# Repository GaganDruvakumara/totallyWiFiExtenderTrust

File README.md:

# Totally A Wifi Extender

### Key Features
* It extends your WiFi
* It uses USB A
* It has a range of a 1-3 meters
* No batteries required
* It makes the range of your WiFi bigger

## PCB
Front (back is just silkscreen & USB pads, you can see in 3d model)

Front

Back

## Bill of Materials
| Reference | Qty | Part                              | Footprint                                                               | Unit Price (USD) | Total Price (USD) |
| --------- | --- | --------------------------------- | ----------------------------------------------------------------------- | ---------------- | ----------------- |
| AE1       | 1   | Antenna                           | RF_Antenna:Texas_SWRA117D_2.4GHz_Left                                   | 1.50             | 1.50              |
| AE2       | 1   | External Antenna / U.FL Connector | Connector_Coaxial:U.FL_Hirose_U.FL-R-SMT-1_Vertical                     | 0.80             | 0.80              |
| C1, C2    | 2   | 100nF Capacitor                   | (assumed 0805) Resistor_SMD:R_0805_2012Metric_Pad1.20x1.40mm_HandSolder | 0.01             | 0.02              |
| D1        | 1   | Zener Diode 5.1V                  | Diode_SMD:D_SOD-123                                                     | 0.05             | 0.05              |
| Q1        | 1   | MMBT3904 NPN Transistor           | Package_TO_SOT_SMD:SOT-23                                               | 0.03             | 0.03              |
| R1        | 1   | 470 Ω Resistor                    | Resistor_SMD:R_0805_2012Metric_Pad1.20x1.40mm_HandSolder                | 0.005            | 0.005             |
| R2, R3    | 2   | 10 kΩ Resistor                    | Resistor_SMD:R_0805_2012Metric_Pad1.20x1.40mm_HandSolder                | 0.005            | 0.01              |
| R4        | 1   | 1 kΩ Resistor                     | Resistor_SMD:R_0805_2012Metric_Pad1.20x1.40mm_HandSolder                | 0.005            | 0.005             |
| R5        | 1   | 220 Ω Resistor                    | Resistor_SMD:R_0805_2012Metric_Pad1.20x1.40mm_HandSolder                | 0.005            | 0.005             |
| R6        | 1   | 100 kΩ Resistor                   | Resistor_SMD:R_0805_2012Metric_Pad1.20x1.40mm_HandSolder                | 0.005            | 0.005             |
| Y1 (Optional)        | 1   | CVCO55xx RF VCO (Mini-Circuits)   | RF_Mini-Circuits:Mini-Circuits_CK605_LandPatternPL-012                  | 5.00             | 5.00              |
Estimated Total Cost: ≈ $7.40 USD

Slack: @gagan222009

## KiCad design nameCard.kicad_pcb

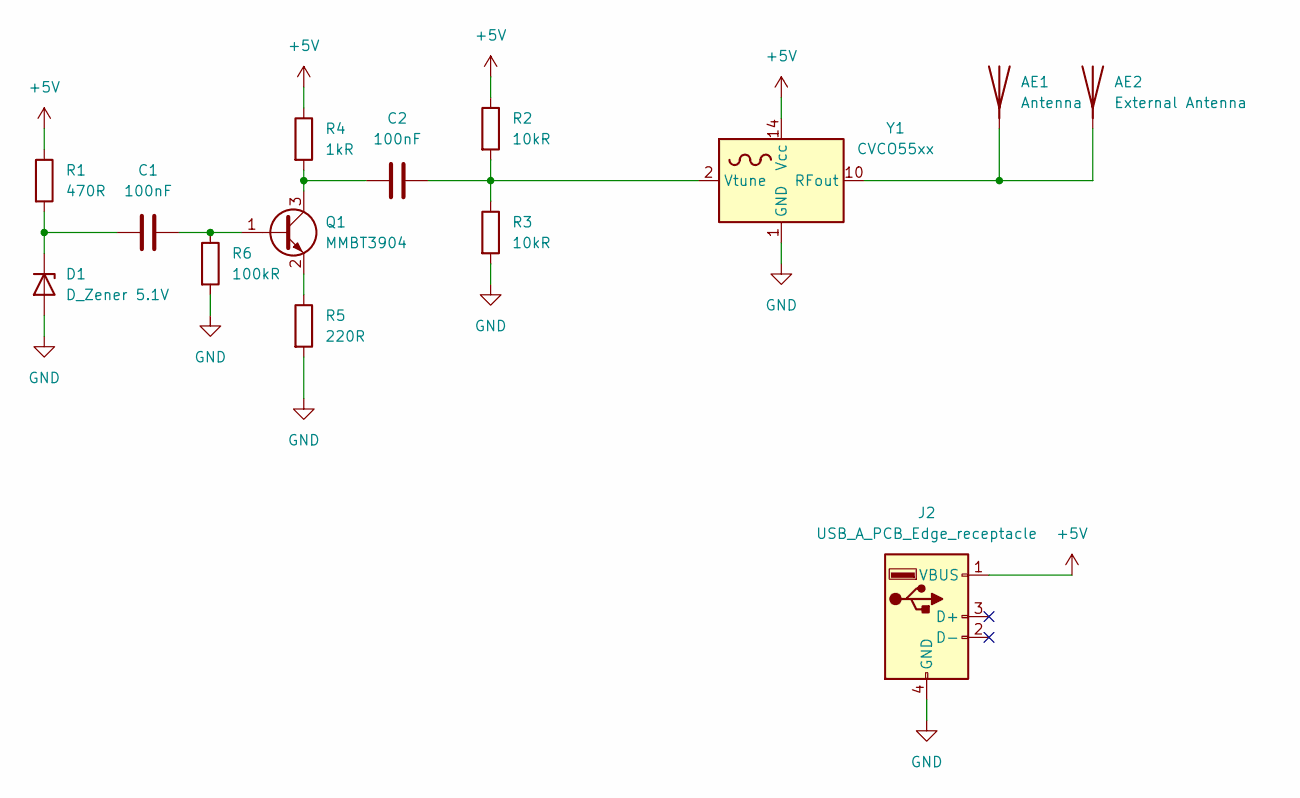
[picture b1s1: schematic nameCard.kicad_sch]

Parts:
AE1: Antenna; Texas_SWRA117D_2.4GHz_Left
AE2: External Antenna; U.FL_Hirose_U.FL-R-SMT-1_Vertical
C1, C2: 100nF; R_0805_2012Metric_Pad1.20x1.40mm_HandSolder
D1: D_Zener 5.1V; D_SOD-123
J2: USB_A_PCB_Edge_receptacle
Q1: MMBT3904; SOT-23
R1: 470R; R_0805_2012Metric_Pad1.20x1.40mm_HandSolder
R2, R3: 10kR; R_0805_2012Metric_Pad1.20x1.40mm_HandSolder
R4: 1kR; R_0805_2012Metric_Pad1.20x1.40mm_HandSolder
R5: 220R; R_0805_2012Metric_Pad1.20x1.40mm_HandSolder
R6: 100kR; R_0805_2012Metric_Pad1.20x1.40mm_HandSolder
Y1: CVCO55xx; Mini-Circuits_CK605_LandPatternPL-012

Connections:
+5V: J2.1 (VBUS), R1.1, R2.1, R4.1, Y1.14 (Vcc)
GND: D1.2 (A), J2.4 (GND), R3.2, R5.2, R6.2, Y1.1 (GND), Y1.3 (GND), Y1.4 (GND), Y1.5 (GND), Y1.6 (GND), Y1.7 (GND), Y1.8 (GND), Y1.9 (GND), Y1.11 (GND), Y1.12 (GND), Y1.13 (GND), Y1.15 (GND), Y1.16 (GND)
unnamed: AE1.1 (A_1), AE2.1 (A_1), Y1.10 (RFout)
unnamed: C1.1, D1.1 (K), R1.2
unnamed: C1.2, Q1.1 (B), R6.1
unnamed: C2.1, Q1.3 (C), R4.2
unnamed: Q1.2 (E), R5.1
unnamed: C2.2, R2.2, R3.1, Y1.2 (Vtune)

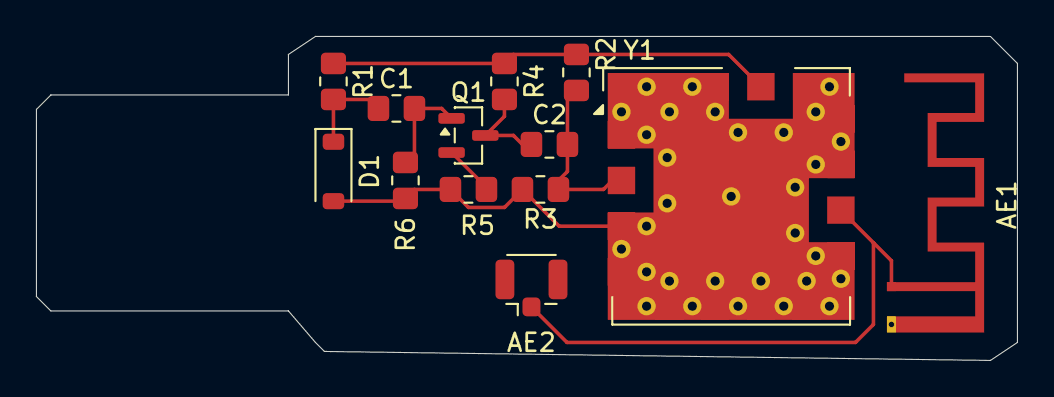
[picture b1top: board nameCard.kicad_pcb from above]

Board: 2 copper layers, 54.5 x 18.0 mm, 14 parts (1 on the bottom side), 8 nets.

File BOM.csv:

Reference,Quantity,Part,Footprint,Unit Price (USD),Total Price (USD)
AE1,1,Antenna,RF_Antenna:Texas_SWRA117D_2.4GHz_Left,1.50,1.50
AE2,1,External Antenna / U.FL Connector,Connector_Coaxial:U.FL_Hirose_U.FL-R-SMT-1_Vertical,0.80,0.80
C1,C2,2,100nF Capacitor,Resistor_SMD:R_0805_2012Metric_Pad1.20x1.40mm_HandSolder,0.01,0.02
D1,1,Zener Diode 5.1V,Diode_SMD:D_SOD-123,0.05,0.05
Q1,1,MMBT3904 (NPN Transistor),Package_TO_SOT_SMD:SOT-23,0.03,0.03
R1,1,470Ω Resistor,Resistor_SMD:R_0805_2012Metric_Pad1.20x1.40mm_HandSolder,0.005,0.005
R2,R3,2,10kΩ Resistor,Resistor_SMD:R_0805_2012Metric_Pad1.20x1.40mm_HandSolder,0.005,0.01
R4,1,1kΩ Resistor,Resistor_SMD:R_0805_2012Metric_Pad1.20x1.40mm_HandSolder,0.005,0.005
R5,1,220Ω Resistor,Resistor_SMD:R_0805_2012Metric_Pad1.20x1.40mm_HandSolder,0.005,0.005
R6,1,100kΩ Resistor,Resistor_SMD:R_0805_2012Metric_Pad1.20x1.40mm_HandSolder,0.005,0.005
Y1,1,CVCO55xx RF Oscillator,RF_Mini-Circuits:Mini-Circuits_CK605_LandPatternPL-012,5.00,5.00
